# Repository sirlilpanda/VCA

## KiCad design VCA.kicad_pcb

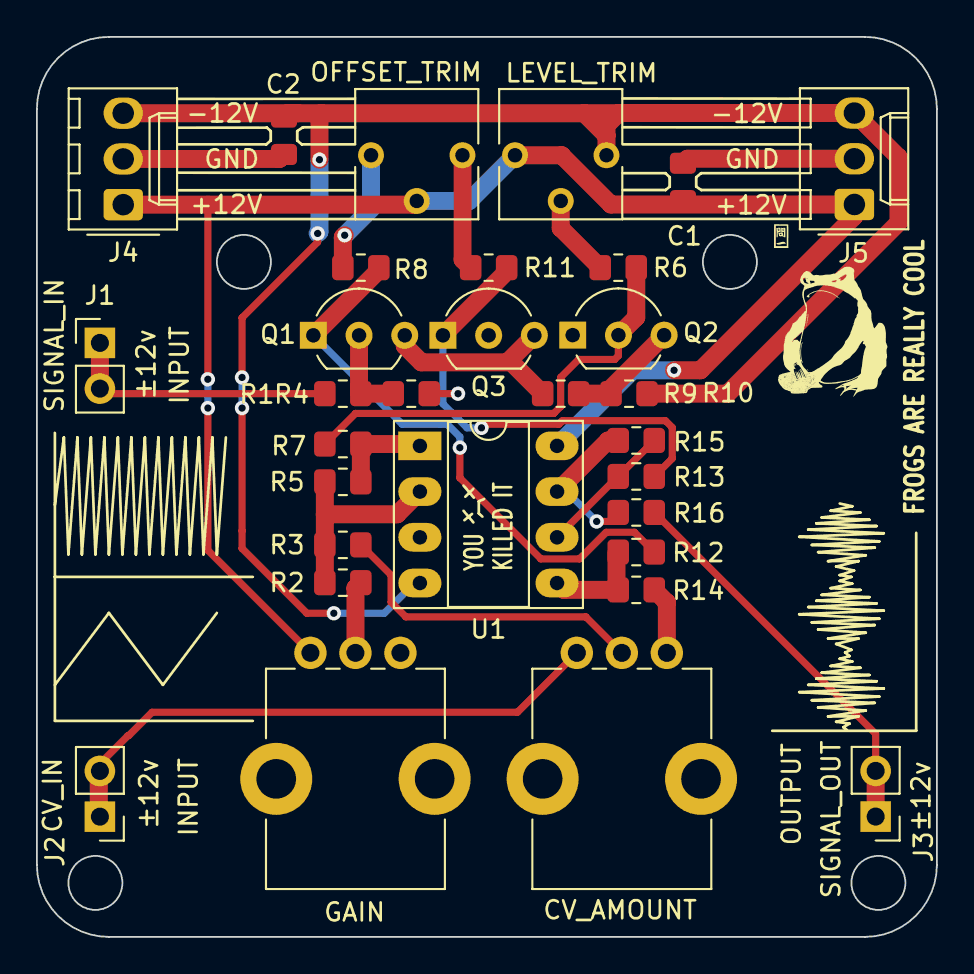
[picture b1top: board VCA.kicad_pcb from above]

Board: 2 copper layers, 50.0 x 50.0 mm, 32 parts (0 on the bottom side), 22 nets.

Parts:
C1, C2: 100n; C_0805_2012Metric_Pad1.18x1.45mm_HandSolder
CV_AMOUNT: 50k; Potentiometer_Bourns_PTV09A-1_Single_Vertical
FROGS ARE REALLY COOL: LOGO; frog3
GAIN: 50k; Potentiometer_Bourns_PTV09A-1_Single_Vertical
J1, J2, J3: Conn_01x02_Socket; PinHeader_1x02_P2.54mm_Vertical
J4, J5: Conn_01x03_Female; Molex_KK-254_AE-6410-03A_1x03_P2.54mm_Vertical
LEVEL_TRIM: 100k; Potentiometer_Vishay_T73YP_Vertical
OFFSET_TRIM: 1k; Potentiometer_Vishay_T73YP_Vertical
Q1, Q2, Q3: BC547; TO-92_Inline_Wide
R1, R14, R15: 220k; R_0805_2012Metric_Pad1.20x1.40mm_HandSolder
R2, R3: 100k; R_0805_2012Metric_Pad1.20x1.40mm_HandSolder
R4: 1K; R_0805_2012Metric_Pad1.20x1.40mm_HandSolder
R5: 47k; R_0805_2012Metric_Pad1.20x1.40mm_HandSolder
R6, R7, R9: 22k; R_0805_2012Metric_Pad1.20x1.40mm_HandSolder
R8, R10, R11, R12, R13: 10k; R_0805_2012Metric_Pad1.20x1.40mm_HandSolder
R16: 1k; R_0805_2012Metric_Pad1.20x1.40mm_HandSolder
U1: TL072; DIP-8_W7.62mm_Socket_LongPads

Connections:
+12V: C1.1, GAIN.1, J4.1, J5.1, LEVEL_TRIM.1, OFFSET_TRIM.2, U1.8 (V+)
-12V: C2.2, J4.3, J5.3, LEVEL_TRIM.3, R10.2, U1.4 (V-)
AMout: J3.1, J3.2, R16.2
GND: C1.2, C2.1, CV_AMOUNT.3, GAIN.3, J4.2, J5.2, Q2.1 (C), Q3.2 (B), R4.2, R14.1, U1.3 (+)
unnamed: CV_AMOUNT.2, R3.1
unnamed: GAIN.2, R2.1
unnamed: LEVEL_TRIM.2, R6.1
unnamed: OFFSET_TRIM.1, R8.1
unnamed: OFFSET_TRIM.3, R11.1
unnamed: Q1.2 (B), R1.2, R4.1
unnamed: Q1.1 (C), R8.2, R12.1
unnamed: Q1.3 (E), Q3.3 (E), R9.1
unnamed: Q2.2 (B), R6.2, R7.2
unnamed: Q2.3 (E), R9.2, R10.1
unnamed: Q3.1 (C), R11.2, R13.1
unnamed: R5.2, R7.1, U1.1
unnamed: R15.2, R16.1, U1.7
unnamed: R2.2, R3.2, R5.1, U1.2 (-)
unnamed: R12.2, R14.2, U1.5 (+)
unnamed: R13.2, R15.1, U1.6 (-)
carrierSignal: J1.1, J1.2, R1.1
controlVoltage: CV_AMOUNT.1, J2.1, J2.2

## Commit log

2023-09-24 inital commit
2023-09-24 added mounting holes
2023-09-25 added more silkscreen
2023-09-25 fixed hopefuly
2023-09-25 fixed?
2023-09-25 reworked layout
2023-09-25 added test points to the schmatic
2023-09-26 updated gbrs
